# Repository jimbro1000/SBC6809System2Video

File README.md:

# SBC6309 Video Inspired by Acorn System 2 #

This started out as a reimplementation of the Acorn system 2 teletext card.
That design quickly went in the bin in favour or something closer to the
video implementation of the BBC Model A/B or Amstrad CPC464.

## Theory of Operation ##

The design is based around a MC6845 CRTC for video timing and sync generation.
This is supplemented with a MC6821 to provide additional control over 
variables outside of the CRTC capability (such as colour palette control)

The conversion of byte data into graphic output is handled by a small CPLD
generating TTL RGB (with a half-bright to facilitate 15 colours).

Optionally the RGB is converted to Chroma and Luma for S-video and Composite
(all in PAL format). Note the RGB doesn't have to be PAL timing but the 
composite will not operate correctly if the timing is abused. Conversion is
performed by a AD724JRZ encoder.

### Clocks ###

The pixel clock is generated on the board starting with a 32MHz oscillator,
this is divided down to 16, 8, 4 or 2MHz. At the same time the data clock is
fixed and synchronised at quarter of the pixel clock.

The choice of divider is controlled by the PIA. Changing the divider requires
the CRTC register values to be reset.

### Video Memory ###

To simplify the design the board uses 16K of dual-port SRAM, this decouples
the main clock of the computer from the video clock, allowing it to run out
of phase without repurcussions. While dual-port ram is expensive, the chip
used here can be obtained at a price comparable to regular SRAM (still more
expensive but not prohibitively so).

From the perspective of the host the video memory is just an 8K window, the
address range is paged via the PIA to expand to the full 16K.

### System Integration ###

The board uses a 16V8 GAL to integrate the board into the rest of the computer
for the purposes of mapping main bus addresses to the video ram and to the CRTC
and PIA.

The main video (RGB) output is through a 9-pin mini-din socket, this incorporates
stereo audio output not generated on this board. The signal can be injected via a
pair of two pin headers.

## Plans ##

### Text Mode ###

The objective is to create a single general purpose video board for the SBC6309
project which must include a text-only mode. To achieve this the board needs to
incorporate a character generator ROM. A set of 256 characters at 8 bytes per
character requires a 2K address space, the CRTC provides row addressing for up
to 32 bytes. Assuming the maximum the requirement increases to 8K but a 8 pixel
x 32 pixel character is of limited use. A more practical solution is to utilise
the 16 byte option and map the rows to 8, 10 or 12. An 8K rom would allow for two
different character sets, possibly at different row counts.

Switching between bitmap and character modes can be performed using a simple
74LS157 multiplexer (two required) depending on the mode. Graphic data can be mapped
to both the multiplexer directly (bitmap) or via the character rom (text).

### Larger Address Space ###

The 6845 can address a maximum of 512KB - way beyond the addressing capability
of the host. With an 8K window that 64 pages. Expanding to a 16K window would make 
this more digestable. The cost of dual-port ram would become excessive however to
take this to the maximum.

Increasing to 32K (or 64K) falls within reasonable design and cost limits.

The mechanism for expanding the address space is the same as used for text mode,
leveraging the row address registers. By adjusting the design for one, the other
becomes inherent.

Referring back to the BBC Model A/B and Amstrad CPC the same trick is used. In
the BBC the row address is effectively the lower 3 bits of the address so that
the bitmap proceeds vertically for 8 bytes before moving to the next horizontal
position. The Amstrad moves the row address on so that each row of video data
is consecutive but vertically jumps 8 rows before returning to the top (offset
by a row) and proceeding again

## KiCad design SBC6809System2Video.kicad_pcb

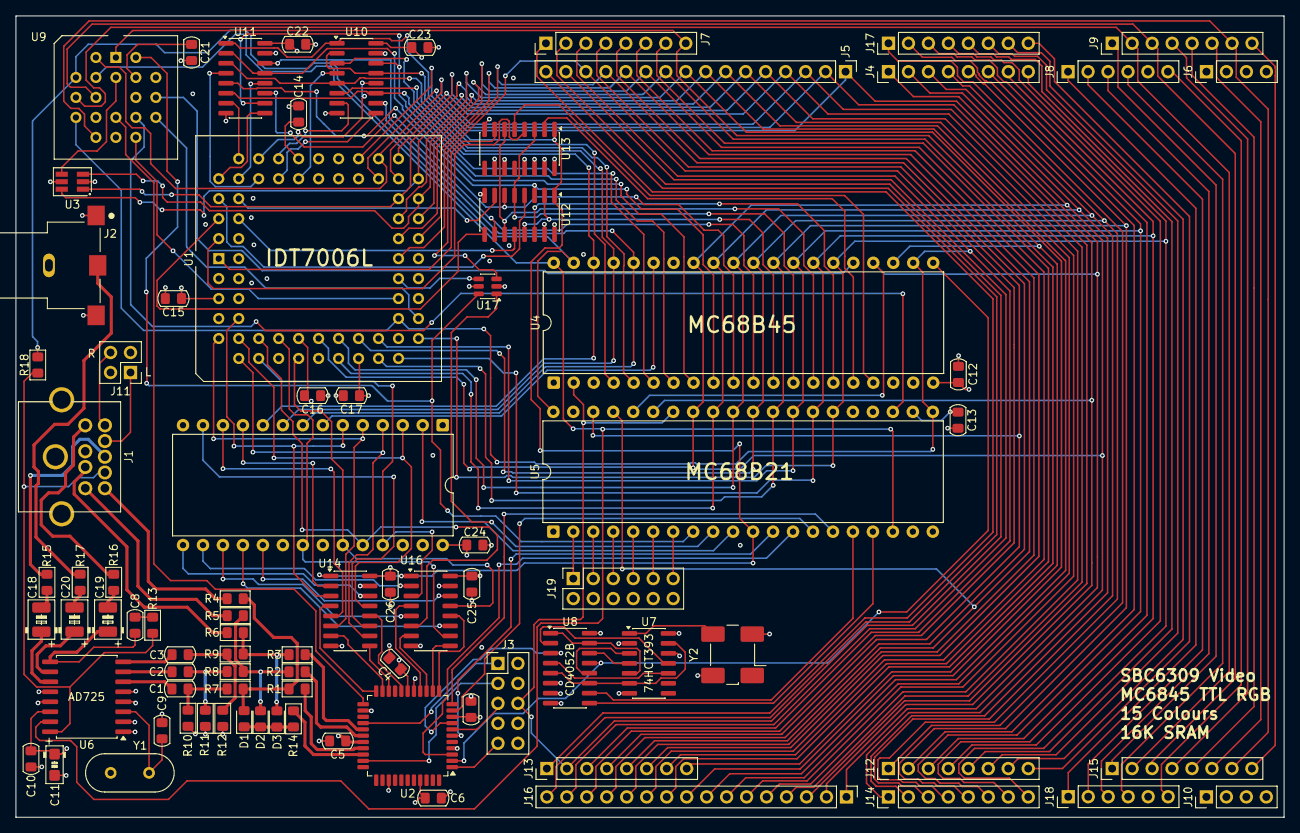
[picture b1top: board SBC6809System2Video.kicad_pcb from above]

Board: 4 copper layers, 161.3 x 101.9 mm, 85 parts (0 on the bottom side), 180 nets.

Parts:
C1, C2, C3, C4, C5, C6, C7, C8, C10, C12, C13, C14, C15, C16, C17, C21, C22, C23, C24, C25, C26: 100nF; C_0805_2012Metric_Pad1.15x1.40mm
C9: 10pF; C_0805_2012Metric_Pad1.15x1.40mm
C11: 10uF; CP_EIA-3216-10_Kemet-I
C18, C19, C20: 220uF; CP_EIA-3528-21_Kemet-B
D1, D2, D3: 1N4148; D_0805_2012Metric_Pad1.15x1.40mm_HandSolder
J1: DIN-9; KMDGX-9S-AS
J2: Conn_Coaxial; CUI_RCJ-013-SMT
J3: JTAG; PinHeader_2x05_P2.54mm_Vertical
J4, J7, J9, J12, J13, J14, J15, J17: Conn_01x08; PinHeader_1x08_P2.54mm_Vertical
J5, J16: Conn_01x16; PinHeader_1x16_P2.54mm_Vertical
J6, J10: Conn_01x04; PinHeader_1x04_P2.54mm_Vertical
J8, J18: Conn_01x06; PinHeader_1x06_P2.54mm_Vertical
J11: Audio; PinHeader_2x02_P2.54mm_Vertical
J19: Spare; PinSocket_2x06_P2.54mm_Vertical
R1, R2, R3, R14, R18: 68R; R_0805_2012Metric_Pad1.15x1.40mm
R4, R5, R6, R7, R8, R9: 150R; R_0805_2012Metric_Pad1.15x1.40mm
R10, R11, R12, R15, R16, R17: 75R; R_0805_2012Metric_Pad1.15x1.40mm
R13: 2K7; R_0805_2012Metric_Pad1.15x1.40mm
U1: IDT7006L35J; PLCC-68_THT-Socket
U2: ATF1504AS-xAx44; TQFP-44_10x10mm_P0.8mm
U3: 74LVC1G10; SOT-23-6_Handsoldering
U4: MC68B45; DIP-40_W15.24mm
U5: MC68B21; DIP-40_W15.24mm
U6: AD725; SOIC-16W_7.5x10.3mm_P1.27mm
U7: 74HCT393; SOIC-14_3.9x8.7mm_P1.27mm
U8: CD4052B; SOIC-16_3.9x9.9mm_P1.27mm
U9: GAL16V8; PLCC-20_THT-Socket
U10, U11, U12, U13, U14, U16: 74LS157; SOIC-16_3.9x9.9mm_P1.27mm
U15: 27C64; DIP-28_W15.24mm
U17: TS5A63157DBV; SOT-23-6
Y1: 4.433618MHz; Crystal_HC49-4H_Vertical
Y2: 32MHz; Oscillator_SMD_Abracon_ASV-4Pin_7.0x5.1mm_HandSoldering

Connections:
+5V: C4.1, C5.1, C6.1, C7.1, C10.1, C11.1, C12.1, C13.1, C14.1, C15.1, C16.1, C17.1, C21.1, C22.1, C23.1, C24.1, C25.1, C26.1, J1.2, J3.4, J6.2, J6.3, J10.2, J10.3, U1.4 (~SEML), U1.5 (R/~WL), U1.17 (VCC), U1.22 (VCC), U1.31 (~SEMR), U1.49 (~INTR), U1.50 (~BUSYR), U1.53 (~BUSYL), U1.54 (~INTL), U1.68 (VCC), U2.9 (VCC), U2.17 (VCC), U2.29 (VCC), U2.41 (VCC), U3.5 (VCC), U4.20 (VCC), U5.20 (VCC), U5.22 (CS0), U5.24 (CS1), U5.25 (ENABLE), U6.1 (NTSC/PAL), U6.4 (AVCC), U6.5 (CE), U6.14 (DVCC), U7.14 (VCC), U8.16 (VDD), U9.20 (VCC), U10.16 (VCC), U11.16 (VCC), U12.16 (VCC), U13.16 (VCC), U14.16 (VCC), U15.27 (~PGM), U15.28 (VCC), U16.16 (VCC), U17.5 (V+), Y2.4 (VDD)
/1MHz: U7.11 (Q0), U8.2 (Y2)
/2MHz: U7.6 (Q3), U7.13 (CP), U8.5 (Y1), U8.11 (X3)
/4MHz: U7.5 (Q2), U8.1 (Y0), U8.15 (X2)
/8MHz: U7.4 (Q1), U8.14 (X1)
/16MHz: U7.3 (Q0), U8.12 (X0)
/500KHz: U7.10 (Q1), U8.4 (Y3)
/Audio-L: J1.8, J11.1
/Audio_R: J1.9, J11.4
/B: J1.1, R6.2
/BFB: R3.1, U2.27 (I/O)
/BLANK: U2.23 (I/O), U9.12 (IO8)
/Bin: C3.1, U6.8 (BLUE)
/CD0: U14.2 (I0a), U15.11 (D0)
/CD1: U14.5 (I0b), U15.12 (D1)
/CD2: U14.11 (I0c), U15.13 (D2)
/CD3: U14.14 (I0d), U15.15 (D3)
/CD4: U15.16 (D4), U16.2 (I0a)
/CD5: U15.17 (D5), U16.5 (I0b)
/CD6: U15.18 (D6), U16.11 (I0c)
/CD7: U15.19 (D7), U16.14 (I0d)
/CRTC_CLK: U2.2 (I/O), U4.21 (CLK), U8.13 (X)
/Ch: C8.2, C19.1, U6.9 (CHROM_OUT)
/ChT: J1.6, R16.2
/Cs: C20.1, U6.10 (CVBS_OUT)
/CsT: J2.1 (In), R17.2
/EXA13: U1.34 (A13R), U17.4
/G: J1.3, R5.2
/GD0: U2.22 (I/O), U14.4 (Za)
/GD1: U2.21 (I/O), U14.7 (Zb)
/GD2: U2.20 (I/O), U14.9 (Zc)
/GD3: U2.18 (I/O), U14.12 (Zd)
/GD4: U2.15 (I/O), U16.4 (Za)
/GD5: U2.14 (I/O), U16.7 (Zb)
/GD6: U2.13 (I/O), U16.9 (Zc)
/GD7: U2.12 (I/O), U16.12 (Zd)
/GFB: R2.1, U2.28 (I/O)
/Gin: C2.1, U6.7 (GREEN)
/HB: R14.1, U2.31 (I/O)
/LOAD_CLK: U2.8 (I/O), U8.3 (Y)
/MA0: U4.4 (MA0), U10.2 (I0a), U10.13 (I1d)
/MA1: U4.5 (MA1), U10.5 (I0b), U11.3 (I1a)
/MA2: U4.6 (MA2), U10.11 (I0c), U11.6 (I1b)
/MA3: U4.7 (MA3), U10.14 (I0d), U11.10 (I1c)
/MA4: U4.8 (MA4), U11.2 (I0a), U11.13 (I1d)
/MA5: U4.9 (MA5), U11.5 (I0b), U12.3 (I1a)
/MA6: U4.10 (MA6), U11.11 (I0c), U12.6 (I1b)
/MA7: U4.11 (MA7), U11.14 (I0d), U12.10 (I1c)
/MA8: U4.12 (MA8), U12.2 (I0a), U12.13 (I1d)
/MA9: U4.13 (MA9), U12.5 (I0b), U13.3 (I1a)
/MA10: U4.14 (MA10), U12.11 (I0c), U13.6 (I1b)
/MA11: U4.15 (MA11), U12.14 (I0d)
/MA12: U4.16 (MA12), U13.2 (I0a)
/MA13: U4.17 (MA13), U13.5 (I0b)
/MD0: U1.8 (I/O0L), U14.3 (I1a), U15.6 (A4)
/MD1: U1.9 (I/O1L), U14.6 (I1b), U15.5 (A5)
/MD2: U1.10 (I/O2L), U14.10 (I1c), U15.4 (A6)
/MD3: U1.11 (I/O3L), U14.13 (I1d), U15.3 (A7)
/MD4: U1.12 (I/O4L), U15.25 (A8), U16.3 (I1a)
/MD5: U1.13 (I/O5L), U15.24 (A9), U16.6 (I1b)
/MD6: U1.15 (I/O6L), U15.21 (A10), U16.10 (I1c)
/MD7: U1.16 (I/O7L), U15.23 (A11), U16.13 (I1d)
/MEM_CE: U1.32 (~CER), U9.13 (IO7)
/MEM_OE: U1.29 (~OER), U9.14 (IO6)
/PA0: J19.1, U5.2 (PA0)
/PA1: J19.3, U5.3 (PA1)
/PA2: J19.5, U5.4 (PA2)
/PA3: J19.7, U5.5 (PA3)
/PA4: J19.9, U5.6 (PA4)
/PA5: J19.11, U5.7 (PA5)
/PA6: U5.8 (PA6), U9.19 (IO1), U17.6
/PA7: U5.9 (PA7), U17.1
/PB0: U5.10 (PB0), U15.2 (A12)
/PB1: U5.11 (PB1), U10.1 (S), U11.1 (S), U12.1 (S), U13.1 (S), U14.1 (S), U16.1 (S)
/PB2: U2.6 (I/O), U5.12 (PB2)
/PB3: U2.3 (I/O), U5.13 (PB3)
/PB4: U2.10 (I/O), U5.14 (PB4)
/PB5: U2.11 (I/O), U5.15 (PB5)
/PB6: U5.16 (PB6), U8.10 (A)
/PB7: U5.17 (PB7), U8.9 (B)
/PIA: U5.23 (~CS2), U9.15 (IO5)
/R: J1.7, R4.2
/RA0: U4.38 (RA0), U10.3 (I1a), U15.10 (A0)
/RA1: U4.37 (RA1), U10.6 (I1b), U15.9 (A1)
/RA2: U4.36 (RA2), U10.10 (I1c), U15.8 (A2)
/RA3: U4.35 (RA3), U15.7 (A3)
/RFB: R1.1, U2.30 (I/O)
/Rin: C1.1, U6.6 (RED)
/VDC: U4.25 (~CS), U9.16 (IO4)
/XA0: U1.55 (A0L), U10.4 (Za)
/XA1: U1.56 (A1L), U10.7 (Zb)
/XA2: U1.57 (A2L), U10.9 (Zc)
/XA3: U1.58 (A3L), U10.12 (Zd)
/XA4: U1.59 (A4L), U11.4 (Za)
/XA5: U1.60 (A5L), U11.7 (Zb)
/XA6: U1.61 (A6L), U11.9 (Zc)
/XA7: U1.62 (A7L), U11.12 (Zd)
/XA8: U1.63 (A8L), U12.4 (Za)
/XA9: U1.64 (A9L), U12.7 (Zb)
/XA10: U1.65 (A10L), U12.9 (Zc)
/XA11: U1.66 (A11L), U12.12 (Zd)
/XA12: U1.67 (A12L), U13.4 (Za)
/XA13: U1.1 (A13L), U13.7 (Zb)
/Y: C18.1, U6.11 (LUM_OUT)
/YT: J1.5, R15.2
/~FS: U4.40 (VS), U5.18 (CB1), U6.15 (VSYNC), U9.5 (I5)
/~HS: R18.2, U4.39 (HS), U5.40 (CA1), U9.4 (I4)
/~HST: J1.4, R13.1, R18.1, U6.16 (HSYNC)
/~SELPH: U3.4, U9.2 (I2)
A0: J5.1, J16.1, U1.48 (A0R), U4.24 (RS), U5.36 (RS0)
A1: J5.2, J16.2, U1.47 (A1R), U5.35 (RS1)
A2: J5.3, J16.3, U1.46 (A2R), U9.3 (I3)
A3: J5.4, J16.4, U1.45 (A3R)
A4: J5.5, J16.5, U1.44 (A4R)
A5: J5.6, J16.6, U1.43 (A5R), U3.6
A6: J5.7, J16.7, U1.42 (A6R), U3.1
A7: J5.8, J16.8, U1.41 (A7R), U3.3
A8: J5.9, J16.9, U1.40 (A8R)
A9: J5.10, J16.10, U1.39 (A9R)
A10: J5.11, J16.11, U1.38 (A10R)
A11: J5.12, J16.12, U1.37 (A11R)
A12: J5.13, J16.13, U1.36 (A12R)
A13: J5.14, J16.14, U17.3
A14: J5.15, J16.15
A15: J5.16, J16.16
AVMA: J12.5, J17.5
BA: J12.2, J17.2
BS: J12.3, J17.3
BUSY: J12.6, J17.6
CLK3: J8.2, J18.2
CLK6: J8.3, J18.3
CLK12: J8.4, J18.4
CLK15: J8.1, J18.1
CLK24: J8.6, J18.6
D0: J4.1, J14.1, U1.19 (I/O0R), U4.33 (D0), U5.33 (D0)
D1: J4.2, J14.2, U1.20 (I/O1R), U4.32 (D1), U5.32 (D1)
D2: J4.3, J14.3, U1.21 (I/O2R), U4.31 (D2), U5.31 (D2)
D3: J4.4, J14.4, U1.23 (I/O3R), U4.30 (D3), U5.30 (D3)
D4: J4.5, J14.5, U1.24 (I/O4R), U4.29 (D4), U5.29 (D4)
D5: J4.6, J14.6, U1.25 (I/O5R), U4.28 (D5), U5.28 (D5)
D6: J4.7, J14.7, U1.26 (I/O6R), U4.27 (D6), U5.27 (D6)
D7: J4.8, J14.8, U1.27 (I/O7R), U4.26 (D7), U5.26 (D7)
DEV0: J9.1, J15.1
DEV1: J9.2, J15.2, U9.6 (I6)
DEV2: J9.3, J15.3, U9.7 (I7)
DEV3: J9.4, J15.4
DEV4: J9.5, J15.5
DEV5: J9.6, J15.6
DEV6: J9.7, J15.7, U9.9 (I9)
DEV7: J9.8, J15.8
E: J12.8, J17.8
GND: C4.2, C5.2, C6.2, C7.2, C9.2, C10.2, C11.2, C12.2, C13.2, C14.2, C15.2, C16.2, C17.2, C21.2, C22.2, C23.2, C24.2, C25.2, C26.2, J1.0 (Shell), J2.2 (Ext), J3.2, J3.10, J6.1, J6.4, J10.1, J10.4, J11.2, J11.3, J19.2, J19.4, J19.6, J19.8, J19.10, J19.12, R10.1, R11.1, R12.1, U1.3 (~CEL), U1.6 (~OEL), U1.14 (GND), U1.18 (GND), U1.35 (GND), U1.52 (GND), U2.4 (GND), U2.16 (GND), U2.24 (GND), U2.36 (GND), U3.2 (GND), U4.1 (GND), U5.1 (VSS), U6.2 (AGND), U6.12 (TRAP), U6.13 (DGND), U7.2 (MR), U7.7 (GND), U7.12 (MR), U8.6 (INH), U8.7 (VEE), U8.8 (VSS), U9.10 (GND), U10.8 (GND), U10.15 (E), U11.8 (GND), U11.15 (E), U12.8 (GND), U12.15 (E), U13.8 (GND), U13.10 (I1c), U13.11 (I0c), U13.13 (I1d), U13.14 (I0d), U13.15 (E), U14.8 (GND), U14.15 (E), U15.14 (GND), U15.20 (~CE), U15.22 (~OE), U16.8 (GND), U16.15 (E), U17.2 (GND), Y1.1, Y2.2 (GND)
LIC: J12.1, J17.1
unnamed: C1.2, R7.2, R10.2
unnamed: C2.2, R8.2, R11.2
unnamed: C3.2, R9.2, R12.2
unnamed: C8.1, R13.2
unnamed: C18.2, R15.1
unnamed: C19.2, R16.1
unnamed: C20.2, R17.1
unnamed: D1.2 (A), R1.2, R4.1, R7.1
unnamed: D1.1 (K), D2.1 (K), D3.1 (K), R14.2
unnamed: D2.2 (A), R2.2, R5.1, R8.1
unnamed: D3.2 (A), R3.2, R6.1, R9.1
unnamed: C9.1, U6.3 (4FSC_CLK), Y1.2
unnamed: U7.1 (CP), Y2.3 (OUT)
Q: J12.7, J17.7
R/~W: J7.3, J13.3, U1.30 (R/~WR), U4.22 (R/~W), U5.21 (R/~W), U9.8 (I8)
TCK: J3.1, U2.26 (I/O/TCK)
TDI: J3.9, U2.1 (I/O/TDI)
TDO: J3.3, U2.32 (I/O/TDO)
TMS: J3.5, U2.7 (I/O/TMS)
TSC: J12.4, J17.4
~E: J7.8, J13.8, U4.23 (E), U9.1 (I1/CLK)
~FIRQ: J7.4, J13.4, U5.38 (~IRQA)
~HALT: J7.1, J13.1
~IRQ: J7.5, J13.5, U5.37 (~IRQB)
~NMI: J7.6, J13.6
~Q: J7.7, J13.7
~RESET: J3.6, J7.2, J13.2, U4.2 (~RESET), U5.34 (~RESET)

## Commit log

2025-12-10 redesign
2025-12-11 convert to dragon
2026-01-18 refresh bom
2026-02-06 fix missing U3
2026-02-19 update fabrication details
2026-02-19 update ibom
2026-03-05 update to include GAL code
